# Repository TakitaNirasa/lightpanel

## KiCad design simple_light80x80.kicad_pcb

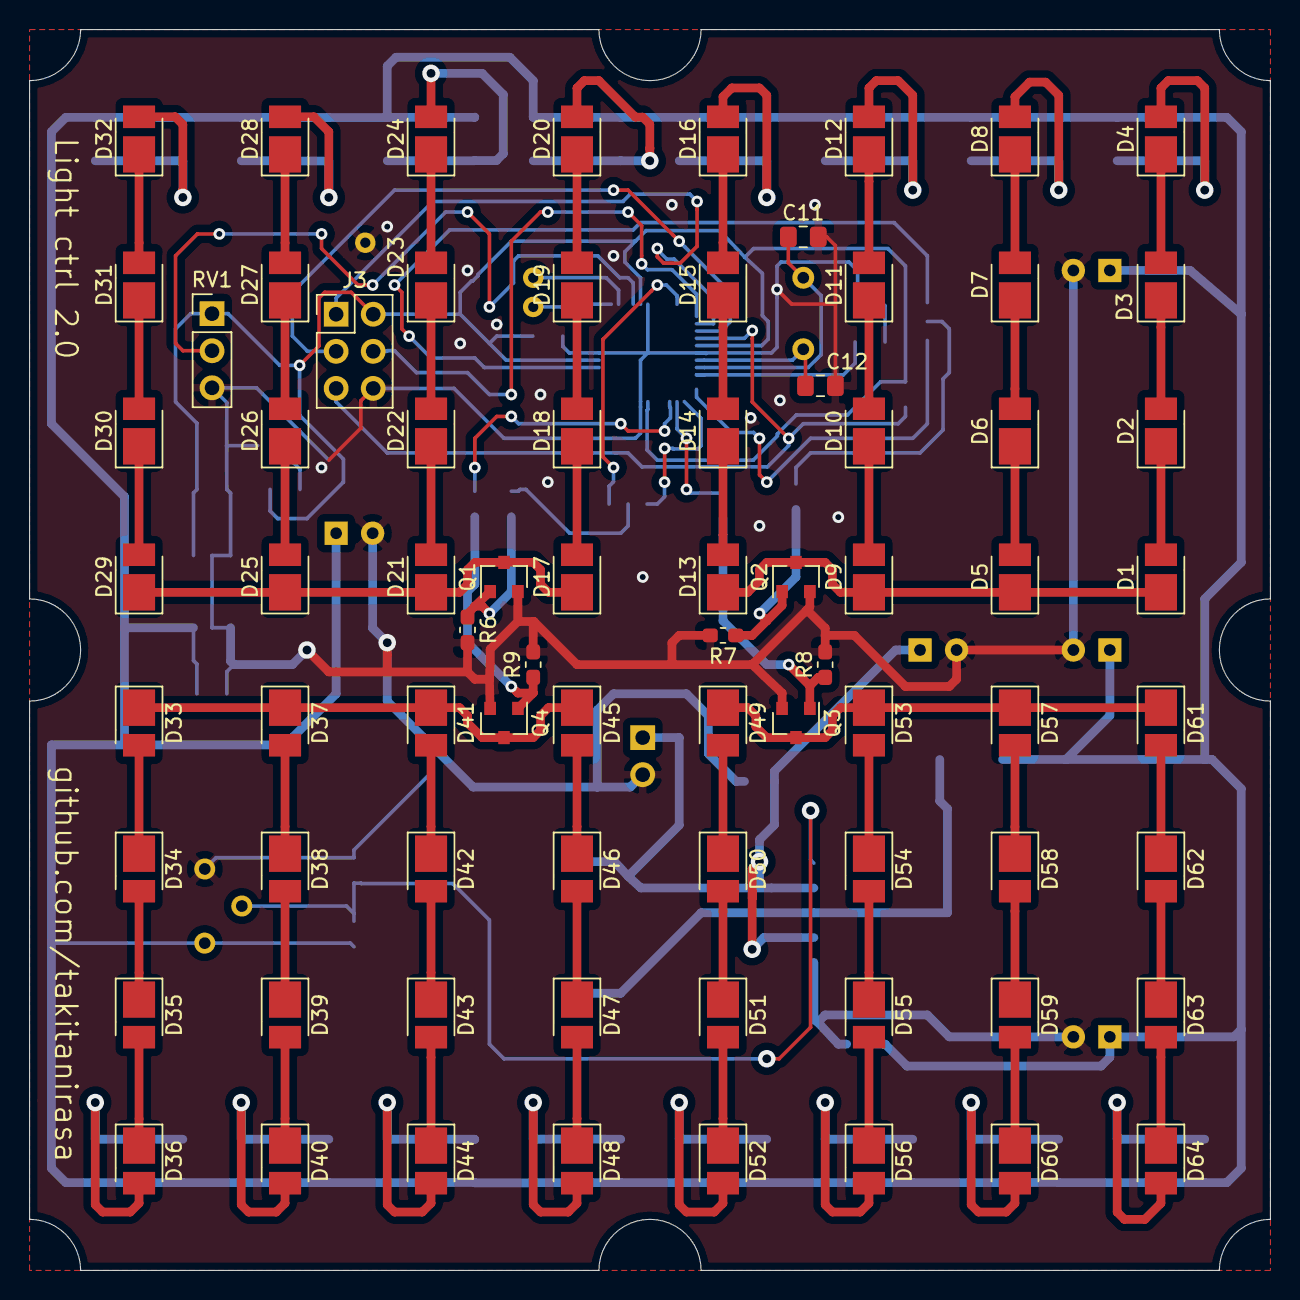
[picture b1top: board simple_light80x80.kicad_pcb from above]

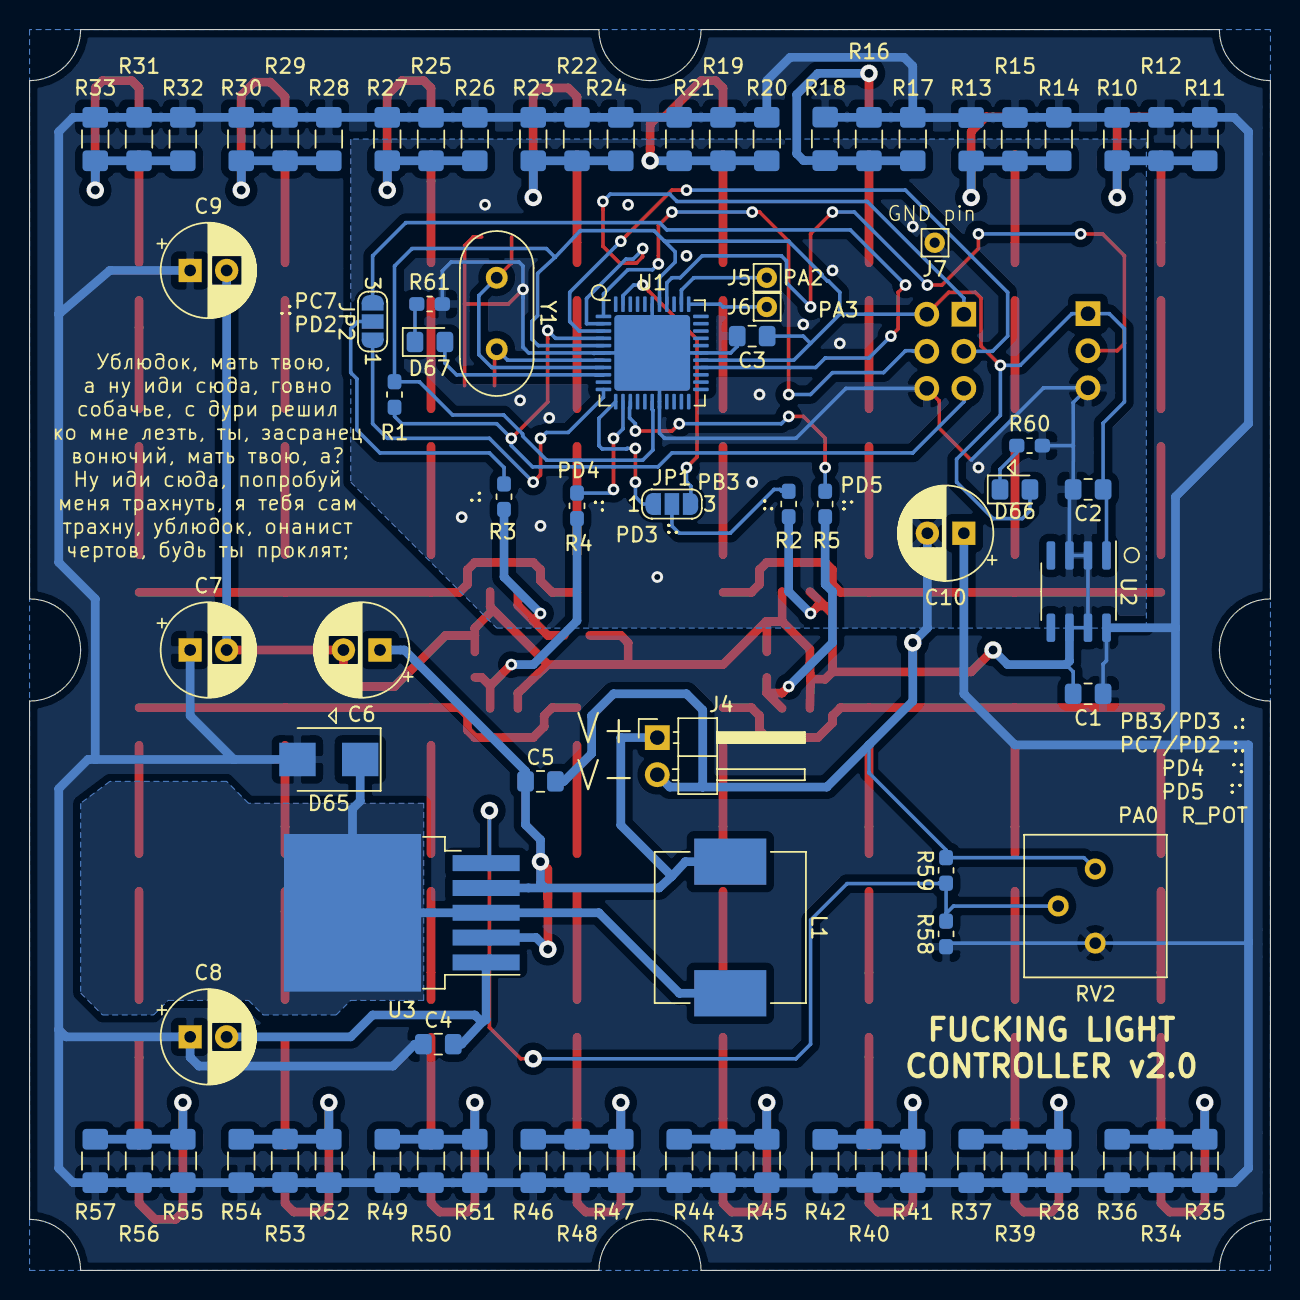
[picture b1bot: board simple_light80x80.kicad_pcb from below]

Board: 2 copper layers, 85.0 x 85.0 mm, 158 parts (82 on the bottom side), 98 nets.

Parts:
C1, C2, C3, C4, C5, C11, C12: C; C_0805_2012Metric_Pad1.15x1.40mm_HandSolder
C6, C7, C8, C9, C10: CP1_Small; CP_Radial_D6.3mm_P2.50mm
D1, D2, D3, D4, D5, D6, D7, D8, D9, D10, D11, D12, D13, D14, D15, D16, D17, D18, D19, D20, D21, D22, D23, D24, D25, D26, D27, D28, D29, D30, D31, D32, D33, D34, D35, D36, D37, D38, D39, D40, D41, D42, D43, D44, D45, D46, D47, D48, D49, D50, D51, D52, D53, D54, D55, D57, D58, D59, D60, D61, D62, D64: LED; LED_PLCC_2835_Handsoldering
D56: 47; LED_PLCC_2835_Handsoldering
D63: 63; LED_PLCC_2835_Handsoldering
D65: DIODE; D_SMB
D66, D67: LED; LED_0805_2012Metric_Pad1.15x1.40mm_HandSolder
J3: AVR-ISP-6; PinHeader_2x03_P2.54mm_Vertical
J4: Conn_01x02_Male; PinHeader_1x02_P2.54mm_Horizontal
J5, J6, J7: Conn_01x01; Pin_D0.7mm_L6.5mm_W1.8mm_FlatFork
JP1, JP2: SolderJumper_3_Open; SolderJumper-3_P1.3mm_Open_RoundedPad1.0x1.5mm_NumberLabels
L1: INDUCTOR; L_Vishay_IHLP-4040
Q1: IRLML003; SOT-23
Q2, Q3, Q4: IRLML0030; SOT-23
R1, R2, R3, R4, R5, R6, R7, R8, R9, R58, R59, R60, R61: R; R_0603_1608Metric_Pad1.05x0.95mm_HandSolder
R10, R11, R12, R13, R14, R15, R16, R17, R18, R19, R20, R21, R22, R23, R24, R25, R26, R27, R28, R29, R30, R31, R32, R33, R34, R35, R36, R37, R38, R39, R40, R41, R42, R43, R44, R45, R46, R47, R48, R49, R50, R51, R52, R53, R54, R55, R56, R57: R; R_1206_3216Metric_Pad1.42x1.75mm_HandSolder
RV1: R_POT; PinHeader_1x03_P2.54mm_Vertical
RV2: R_POT; Potentiometer_Bourns_3386P_Vertical
U1: ATmega32A-MU; QFN-44-1EP_7x7mm_P0.5mm_EP5.2x5.2mm
U2: L78L05_SO8; SOIC-8_3.9x4.9mm_P1.27mm
U3: XL6009; TO-263-5_TabPin3
Y1: Crystal; Crystal_HC18-U_Vertical

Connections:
+5V: C2.1, C3.1, D66.2, J3.2, R1.1, RV1.1, U1.5, U1.17, U1.27, U1.38, U2.1
+12V: C1.1, C4.1, C7.1, C8.1, C9.1, C10.1, D65.2, R10.1, R11.1, R12.1, R13.1, R14.1, R15.1, R16.1, R17.1, R18.1, R19.1, R20.1, R21.1, R22.1, R23.1, R24.1, R25.1, R26.1, R27.1, R28.1, R29.1, R30.1, R31.1, R32.1, R33.1, R34.1, R35.1, R36.1, R37.1, R38.1, R39.1, R40.1, R41.1, R42.1, R43.1, R44.1, R45.1, R46.1, R47.1, R48.1, R49.1, R50.1, R51.1, R52.1, R53.1, R54.1, R55.1, R56.1, R57.1, R58.1, RV2.3, U2.8
+BATT: C5.1, C6.1, J4.1, L1.1, U3.2, U3.4
/MISO: J3.1, U1.2
/MOSI: J3.4, U1.1
/RST: J3.5, R1.2, U1.4
/SCK: J3.3, U1.3
/osc1: C11.1, U1.8, Y1.1
/osc2: C12.1, U1.7, Y1.2
/test_led: D67.2, U1.9
GND: C1.2, C2.2, C3.2, C4.2, C5.2, C6.2, C7.2, C8.2, C9.2, C10.2, C11.2, C12.2, J3.6, J4.2, J7.1, Q1.2, Q2.2, Q3.2, Q4.2, R6.2, R7.2, R8.2, R9.2, R59.2, R60.1, R61.1, RV1.3, RV2.1, U1.6, U1.18, U1.28, U1.39, U1.45, U2.2, U2.3, U2.6, U2.7, U3.1
unnamed: D1.1, D5.1, D9.1, D13.1, Q2.3
unnamed: D1.2, D2.1
unnamed: D2.2, D3.1
unnamed: D3.2, D4.1
unnamed: D4.2, R31.2, R32.2, R33.2
unnamed: D5.2, D6.1
unnamed: D6.2, D7.1
unnamed: D7.2, D8.1
unnamed: D8.2, R28.2, R29.2, R30.2
unnamed: D9.2, D10.1
unnamed: D10.2, D11.1
unnamed: D11.2, D12.1
unnamed: D12.2, R25.2, R26.2, R27.2
unnamed: D13.2, D14.1
unnamed: D14.2, D15.1
unnamed: D15.2, D16.1
unnamed: D16.2, R22.2, R23.2, R24.2
unnamed: D17.1, D21.1, D25.1, D29.1, Q1.3
unnamed: D17.2, D18.1
unnamed: D18.2, D19.1
unnamed: D19.2, D20.1
unnamed: D20.2, R19.2, R20.2, R21.2
unnamed: D21.2, D22.1
unnamed: D22.2, D23.1
unnamed: D23.2, D24.1
unnamed: D24.2, R16.2, R17.2, R18.2
unnamed: D25.2, D26.1
unnamed: D26.2, D27.1
unnamed: D27.2, D28.1
unnamed: D28.2, R13.2, R14.2, R15.2
unnamed: D29.2, D30.1
unnamed: D30.2, D31.1
unnamed: D31.2, D32.1
unnamed: D32.2, R10.2, R11.2, R12.2
unnamed: D33.1, D37.1, D41.1, D45.1, Q4.3
unnamed: D33.2, D34.1
unnamed: D34.2, D35.1
unnamed: D35.2, D36.1
unnamed: D36.2, R34.2, R35.2, R36.2
unnamed: D37.2, D38.1
unnamed: D38.2, D39.1
unnamed: D39.2, D40.1
unnamed: D40.2, R37.2, R38.2, R39.2
unnamed: D41.2, D42.1
unnamed: D42.2, D43.1
unnamed: D43.2, D44.1
unnamed: D44.2, R40.2, R41.2, R42.2
unnamed: D45.2, D46.1
unnamed: D46.2, D47.1
unnamed: D47.2, D48.1
unnamed: D48.2, R43.2, R44.2, R45.2
unnamed: D49.1, D53.1, D57.1, D61.1, Q3.3
unnamed: D49.2, D50.1
unnamed: D50.2, D51.1
unnamed: D51.2, D52.1
unnamed: D52.2, R46.2, R47.2, R48.2
unnamed: D53.2, D54.1
unnamed: D54.2, D55.1
unnamed: D55.2, D56.1
unnamed: D56.2, R49.2, R50.2, R51.2
unnamed: D57.2, D58.1
unnamed: D58.2, D59.1
unnamed: D59.2, D60.1
unnamed: D60.2, R52.2, R53.2, R54.2
unnamed: D61.2, D62.1
unnamed: D62.2, D63.1
unnamed: D63.2, D64.1
unnamed: D64.2, R55.2, R56.2, R57.2
unnamed: D65.1, L1.2, U3.3
unnamed: D66.1, R60.2
unnamed: D67.1, R61.2
unnamed: J5.1, U1.35
unnamed: J6.1, U1.34
unnamed: JP1.1, U1.12
unnamed: JP1.2, R2.2
unnamed: JP1.3, U1.43
unnamed: JP2.1, U1.11
unnamed: JP2.2, R3.2
unnamed: JP2.3, U1.26
unnamed: Q1.1, R2.1, R6.1
unnamed: Q2.1, R3.1, R7.1
unnamed: Q3.1, R4.1, R8.1
unnamed: Q4.1, R5.1, R9.1
unnamed: R4.2, U1.13
unnamed: R5.2, U1.14
unnamed: R58.2, R59.1, RV2.2, U3.5
unnamed: RV1.2, U1.37

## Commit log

2021-09-23 Adding prj files
2021-09-23 Scrinshots added
